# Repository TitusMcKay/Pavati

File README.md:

so here is some text in the md file idk how to ***write*** md but i should eventualy lol

i learned how to ssh keygen and use that for auth and can now push this new line over ssh
# About
In this repo are files for the battery signal delay box for the Pavati boats
The pcb designs were done in KiCad
The 3d models will be done in FreeCAD

# How To Source Components
To select components for procurment see [procurment.md](./procurment.md)

There is a [bom](https://en.wikipedia.org/wiki/Bill_of_materials) in [battery switch delay.tsv](./battery%20switch%20delay.tsv) that can be used to place manufatuer part numbers on the procurment list 

# How to view
## PCB
To view in the web go [here](https://kicanvas.org/?repo=https%3A%2F%2Fgithub.com%2FTitusMcKay%2FPavati)

To view on your machine clone the repo and open the project in KiCad

## 3D
You can view the case [here](https://3dviewer.net/#model=https://raw.githubusercontent.com/TitusMcKay/Pavati/refs/heads/master/3d/case.step).

If you want the best viewing experience open the [design files](./3d) in [FreeCAD](https://github.com/freecad/freecad), or open .step files in your 3d printer slicer or CAD software of choice

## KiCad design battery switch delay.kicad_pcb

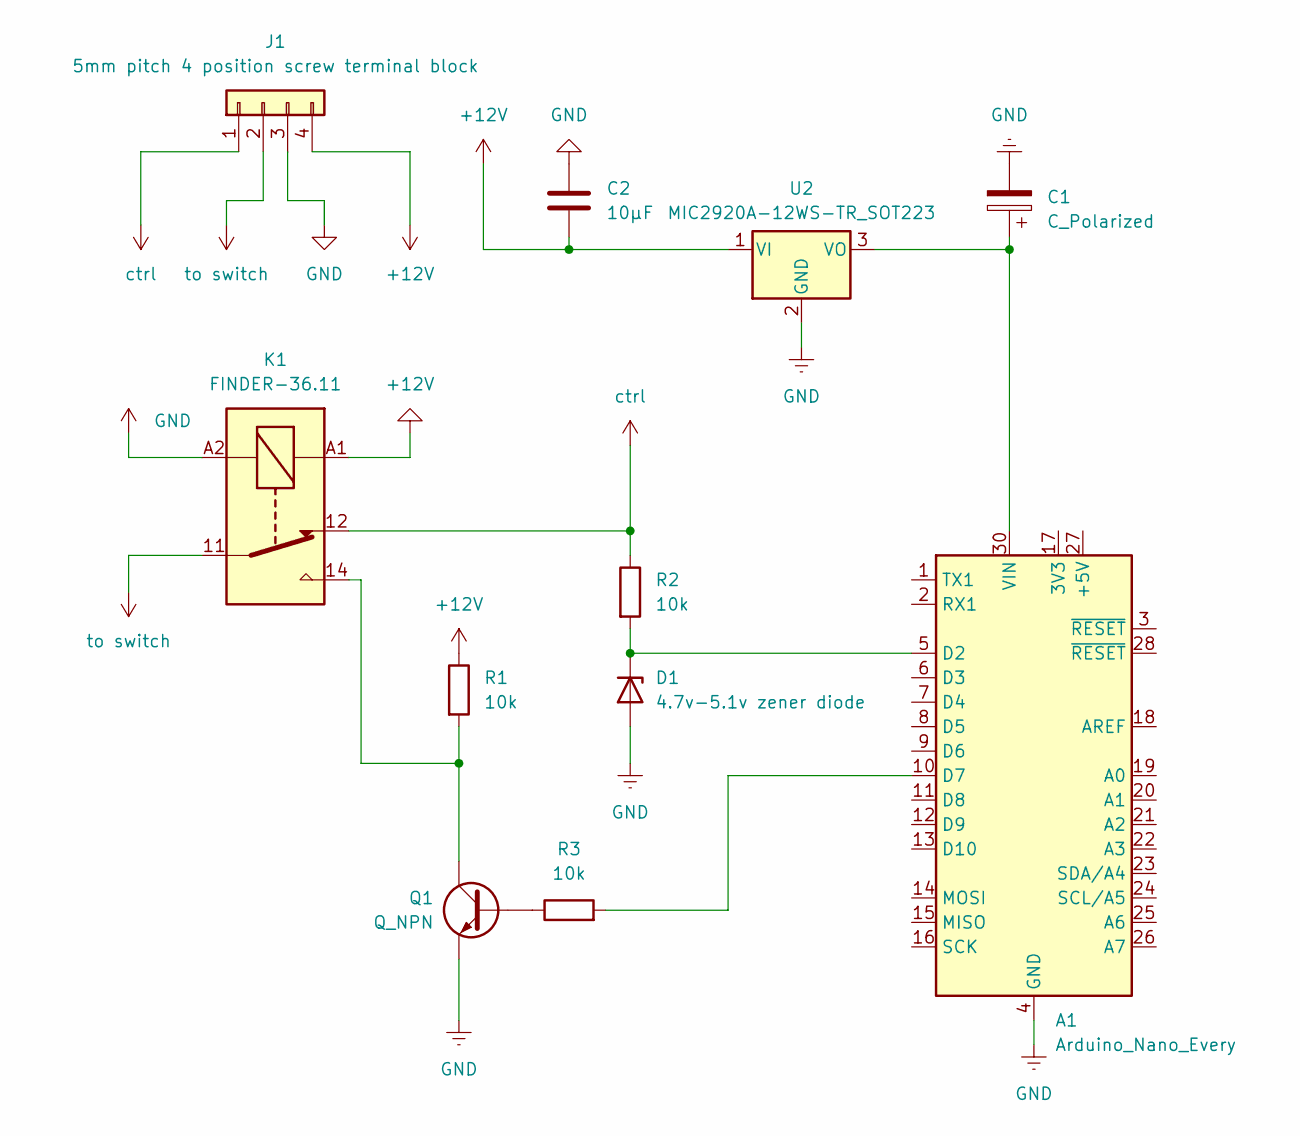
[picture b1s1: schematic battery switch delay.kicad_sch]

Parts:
A1: Arduino_Nano_Every; Arduino_Nano
C1: C_Polarized
C2: 10μF; C_0805_2012Metric_Pad1.18x1.45mm_HandSolder
D1: 4.7v-5.1v zener diode; D_SOD-123
J1: 5mm pitch 4 position screw terminal block; TerminalBlock_MaiXu_MX126-5.0-04P_1x04_P5.00mm
K1: FINDER-36.11; Relay_SPDT_Finder_36.11
Q1: Q_NPN; SOT-23
R1, R2, R3: 10k; R_0805_2012Metric_Pad1.20x1.40mm_HandSolder
U2: MIC2920A-12WS-TR_SOT223; SOT-223-3_TabPin2

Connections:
+12V: C2.2, J1.4, K1.A1, R1.1, U2.1 (VI)
GND: A1.4 (GND), A1.29 (GND), C1.2, C2.1, D1.2 (A), J1.3, K1.A2, Q1.2 (E), U2.2 (GND)
unnamed: A1.5 (D2), D1.1 (K), R2.2
unnamed: A1.10 (D7), R3.2
unnamed: A1.30 (VIN), C1.1, U2.3 (VO)
unnamed: Q1.1 (B), R3.1
unnamed: K1.14, Q1.3 (C), R1.2
ctrl: J1.1, K1.12, R2.1
to switch: J1.2, K1.11

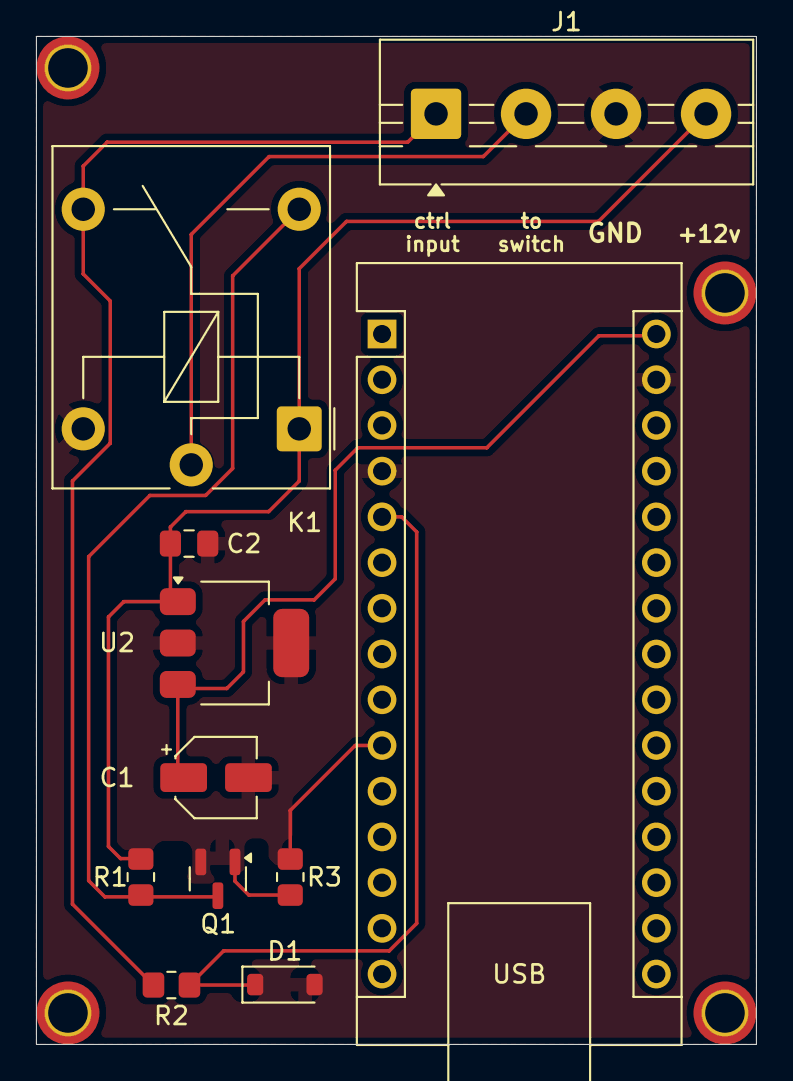
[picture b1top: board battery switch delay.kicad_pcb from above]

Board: 2 copper layers, 40.0 x 56.0 mm, 11 parts (0 on the bottom side), 9 nets.

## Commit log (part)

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2026-03-10 added readme
2026-03-10 fixed spelling and did bold italic
2026-03-10 trying multiple lines here gonna add the
2026-03-11 removed test
    '
2026-03-11 second push with ssh, yay
2026-03-11 playing with md more
2026-03-11 added info about the project
2026-03-11 added description field to bom
2026-03-11 changed the description of caps to include voltage rating
2026-03-11 generated bom
2026-03-12 trying ssh agent
2026-03-12 added procurment procurment.md and structure inside
2026-03-12 readme
2026-03-12 more readme
2026-03-12 grammer in readme
2026-03-12 procurment formatting fix
2026-03-13 added capacitor part numbers to procurment.md
2026-03-13 added zener diodes
2026-03-13 added more parts to procurement.md
2026-03-13 going to bed now
2026-03-13 added viewing instructions to readme
2026-03-13 trying html open in new tab
2026-03-13 trying again
2026-03-13 didnt work
2026-03-15 added resistors and voltage regulator part numbers
2026-03-15 added transistors to procurment
2026-03-16 got the transistor the correct footprint hopefully
2026-03-16 shuffling things around
2026-03-16 more of the same
2026-03-17 did more board layout and actualy have all nets connected. looking at drc so i can be sure
2026-03-17 forgor to save lol
2026-03-17 commented out TI voltage regulator from procurement.md
2026-03-17 moved overlaping text in schematic
2026-03-17 test commit
2026-03-17 moved another thing
2026-03-18 changed the cap on the voltage regulator in the schematic and baord
2026-03-18 more rand changes ig
2026-03-18 moved a trace
2026-03-18 changed readme link kicanvas
2026-03-18 testing
2026-03-18 incriment
2026-03-18 testing kicanvas
2026-03-19 changed relay to smth with a much lower price .63 vs /bin/zsh.70 🤯
2026-03-19 debuging kicanvas
2026-03-20 probably ready for first order
2026-03-20 moved text
2026-03-21 zipped up gerbers
2026-03-21 moved some silk screen text
2026-03-28 barely anything
2026-03-29 trying code blocks
2026-03-29 trying again but fr this time
2026-03-29 the llm did lang things better
2026-03-29 working better
2026-03-29 better
2026-03-29 poking around
2026-03-29 poking around more
2026-03-29 making progress
2026-03-29 did all of it
2026-03-29 found cheaper terminal blocks
2026-03-30 added qr code and text to the repo
2026-03-30 fixed ground pour to include the relay
2026-04-01 did a quick mockup of the case
2026-04-01 added 3d folder
2026-04-01 exported case to a step
2026-04-01 removed .history
2026-04-12 wrote simple code
2026-04-13 changed readme
2026-04-27 made code gooder
2026-05-02 made code even gooder
2026-05-06 compiles code without errors other than dev setup, tested at pavati but waits for 2 seconds after power on before immedietly setting switch pin to high
2026-05-06 smol change
2026-05-06 reset timer if pin d2 ever touches low
2026-05-08 got nowhere but ik that fob and switch pins are low
2026-05-08 verified that timer works by setting timer activation on fob low, after two seconds the switch pin went high. when testing at pavati both fob and switch pins stayed low the entire time. still dont kn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
2026-05-10 pushing to repo idk when commit last lol
2026-05-13 made better version of case, still needs lid to be designed. i will have to add a grove for o-ring gasket and screw holes to hold it down. the box still has no way to mounting to a boat so ill have t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
2026-05-15 this shi with git should be fixed now
2026-05-15 conna push grandfather case again
2026-05-18 added channel for o-ring. also added screw holes for lid
2026-05-18 simple things on case
2026-05-19 added screws to procurement.md
2026-05-19 trying md
2026-05-20 added mcmaster oring
2026-06-03 made channel narrow for better oring seal
2026-06-15 added pricing spreadsheet with component costs from digikey. also added arduino from dfrobot and header to procurement.md
2026-06-18 6 second delay before signal is sent
2026-06-22 added wire and pricing info. will meet with Chuck tomorrow to talk about selling or sm idk lol
2026-06-24 added the ability to abort poweroff if the user sets fob pin to high for just a little bit, will test on boat tomorrow
2026-06-24 dumb commit
2026-06-24 removed smol delay at begining
2026-06-24 will only abort power off if signal is received and is between .25 and 2 seconds long
2026-06-30 making tag
